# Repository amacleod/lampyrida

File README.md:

Lampyrida Macro Pad
===================

Just a small project for me to practice SK6812 RGB LED soldering.

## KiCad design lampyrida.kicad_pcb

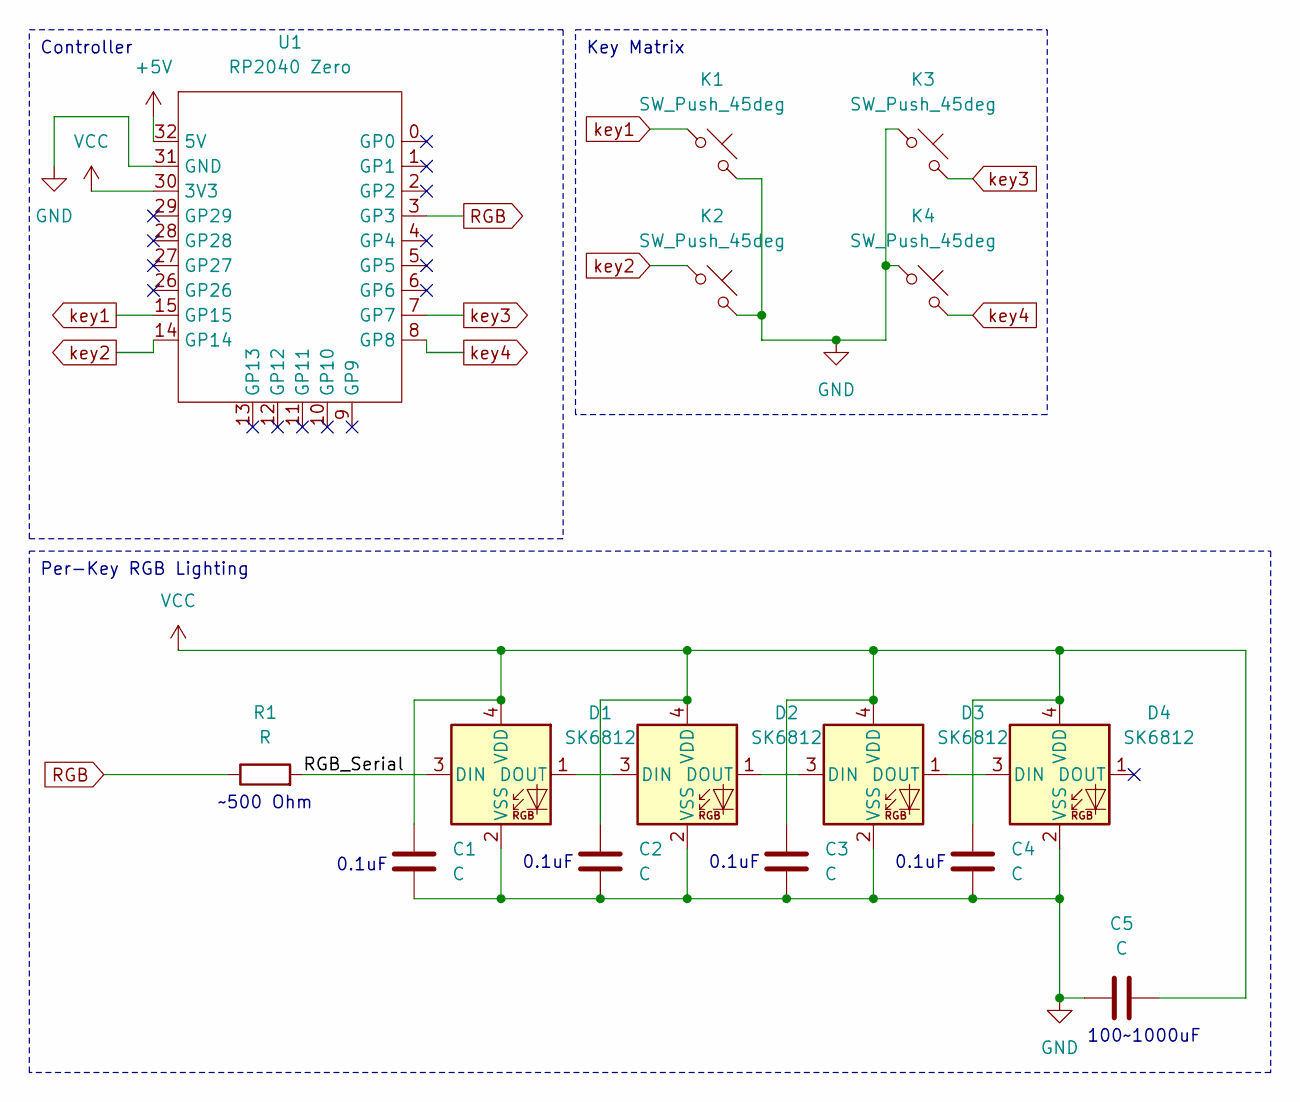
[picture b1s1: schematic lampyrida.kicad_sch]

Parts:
C1, C2, C3, C4, C5: C; C_1206_3216Metric_Pad1.33x1.80mm_HandSolder
D1, D2, D3, D4: SK6812; LED_RGB_SK6812Mini-E
K1, K2, K3, K4: SW_Push_45deg; Socket_PG1350_Hotswap
R1: R; R_1206_3216Metric_Pad1.30x1.75mm_HandSolder
U1: RP2040 Zero; RP2040 Zero (Through Hole)

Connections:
+5V: U1.32 (5V)
/RGB_Serial: D1.3 (DIN), R1.2
GND: C1.1, C2.1, C3.1, C4.1, C5.2, D1.2 (VSS), D2.2 (VSS), D3.2 (VSS), D4.2 (VSS), K1.2, K2.2, K3.1, K4.1, U1.31 (GND)
unnamed: D1.1 (DOUT), D2.3 (DIN)
unnamed: D2.1 (DOUT), D3.3 (DIN)
unnamed: D3.1 (DOUT), D4.3 (DIN)
RGB: R1.1, U1.3 (GP3)
VCC: C1.2, C2.2, C3.2, C4.2, C5.1, D1.4 (VDD), D2.4 (VDD), D3.4 (VDD), D4.4 (VDD), U1.30 (3V3)
key1: K1.1, U1.15 (GP15)
key2: K2.1, U1.14 (GP14)
key3: K3.2, U1.7 (GP7)
key4: K4.2, U1.8 (GP8)

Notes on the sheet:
Key Matrix
Per-Key RGB Lighting
Controller
0.1uF
100~1000uF
~500 Ohm

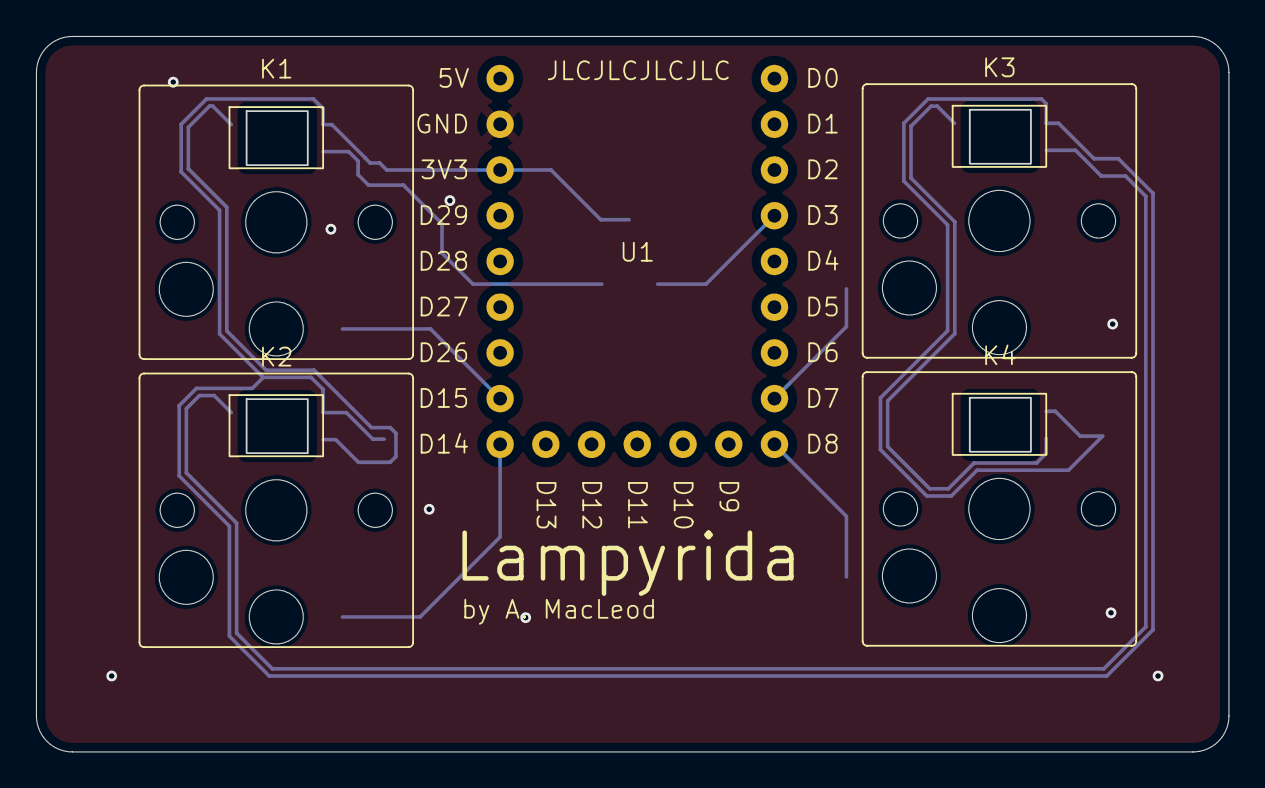
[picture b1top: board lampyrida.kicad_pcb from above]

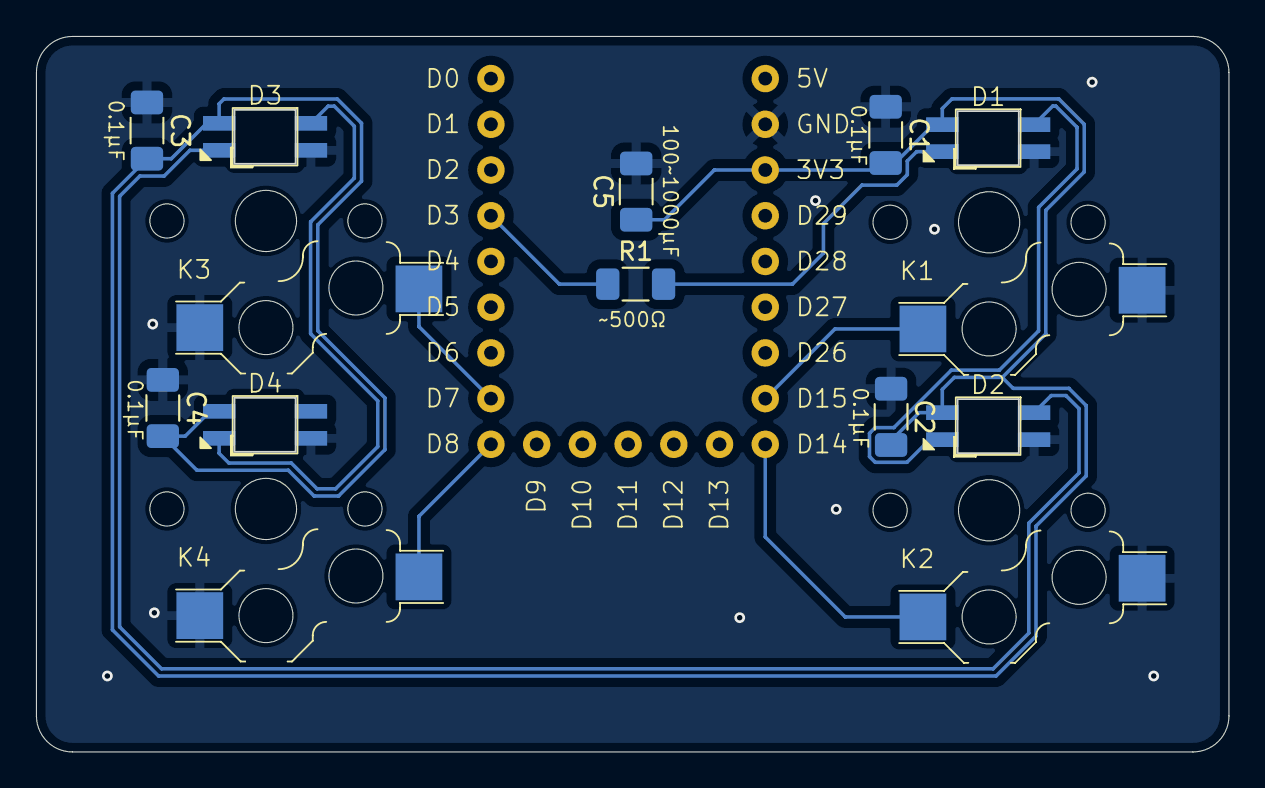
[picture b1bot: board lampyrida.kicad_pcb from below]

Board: 2 copper layers, 66.2 x 39.8 mm, 15 parts (6 on the bottom side), 11 nets.

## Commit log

2025-02-08 Lampyrida macropad v0.0.1
2025-02-08 MIT license.
2025-02-08 Update LICENSE
2025-02-26 Added Kee Boar KB2040 to the symbol library.
2025-03-23 Add R1, improve ground plane, add labels.
    Fixes #7 by making more room for the ground pour to go around things
    and with some better-placed vias.
    Fixes #6 by adding labels, both in schematic and PCB, for capacitors
    and the new resistor.
    Fixes #5 by adding a spot for a 500-ish Ohm resistor on the LED data
    input line.
2025-03-23 Fixes #4 by swapping which end of K3 and K4 is connected to ground.
2025-05-13 Removing level shifter to use 3.3V power and signal with SK2812 LEDs.
2025-05-13 Rerouting traces with new non-5V net.
2025-05-18 Fixing SK6812-MiniE footprint and rerouting traces to match.
2025-05-18 Fixing SK6812-MiniE footprint and rerouting traces to match. (#8)
2025-05-19 Correcting DRC violations.
2025-05-19 Adding render of Lampyrida front side.
